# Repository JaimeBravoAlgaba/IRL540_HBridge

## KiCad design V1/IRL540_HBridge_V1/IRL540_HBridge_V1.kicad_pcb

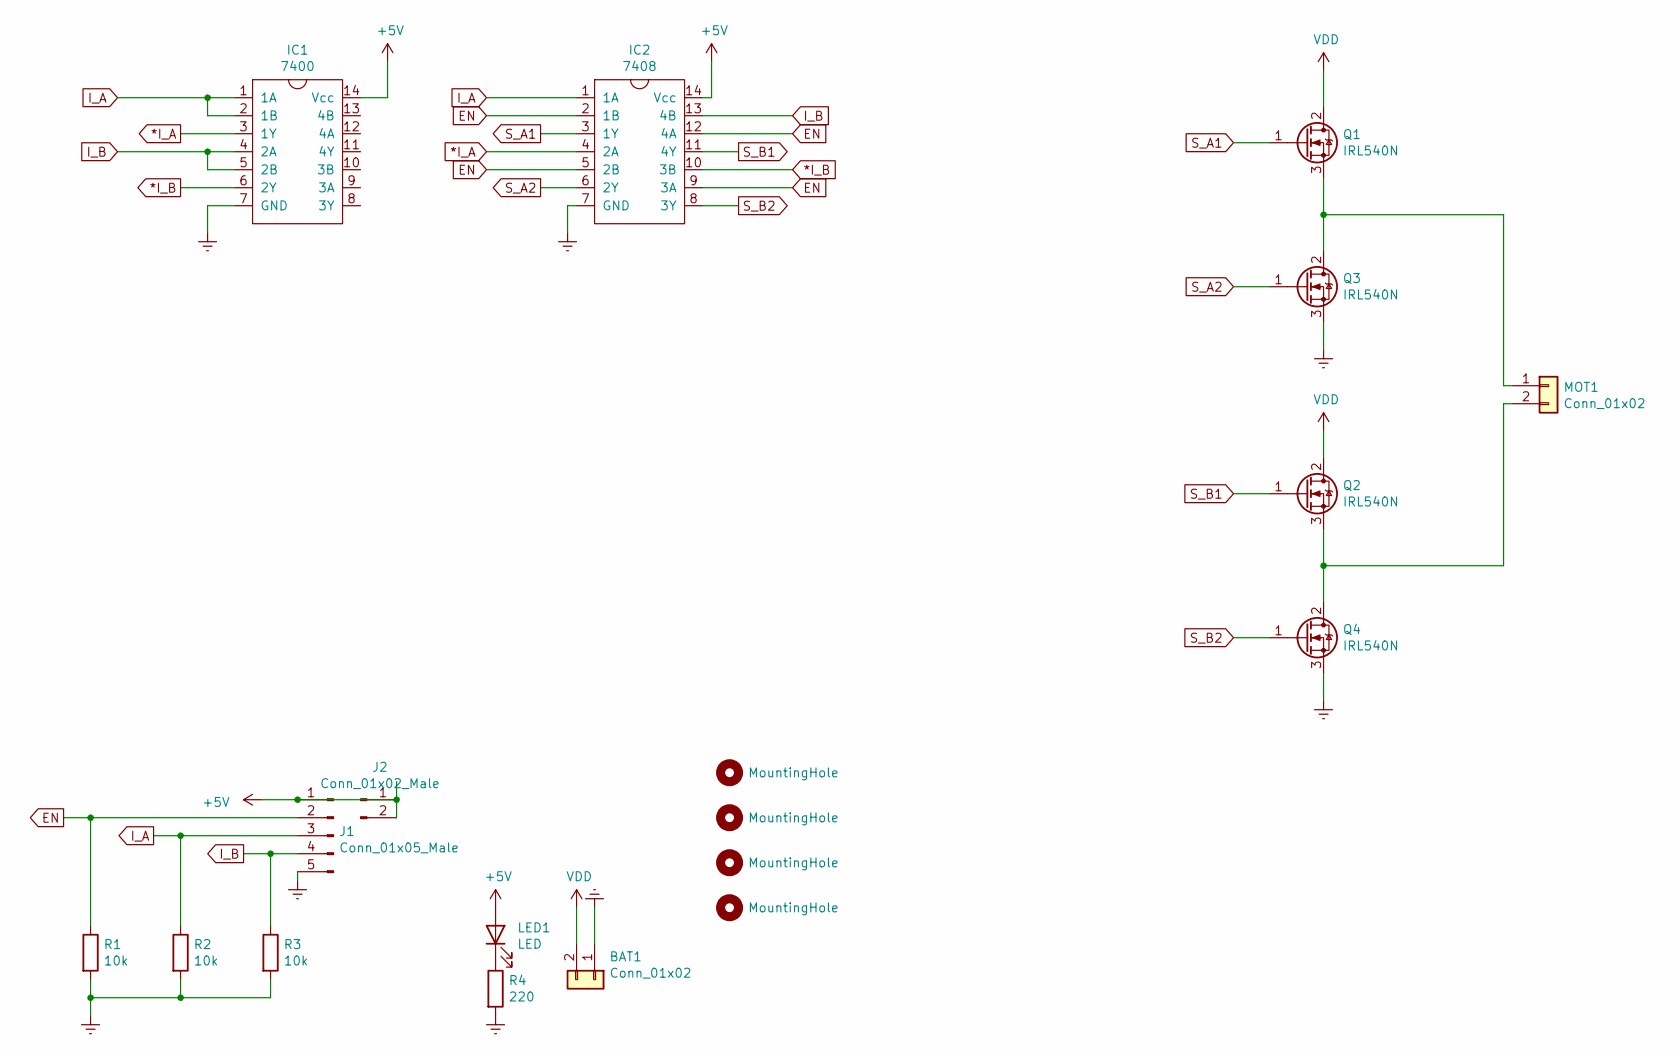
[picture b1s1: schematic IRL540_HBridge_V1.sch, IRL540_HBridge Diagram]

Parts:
BAT1: Conn_01x02; JWT_A3963_1x02_P3.96mm_Vertical
H1, H2, H3, H4: MountingHole; MountingHole_3.2mm_M3
IC1: 7400; DIP-14_W7.62mm
IC2: 7408; DIP-14_W7.62mm
J1: Conn_01x05_Male; PinHeader_1x05_P2.54mm_Vertical
J2: Conn_01x02_Male; PinHeader_1x02_P2.54mm_Vertical
LED1: LED; LED_D3.0mm
MOT1: Conn_01x02; JWT_A3963_1x02_P3.96mm_Vertical
Q1, Q2, Q3, Q4: IRL540N; TO-220-3_Vertical
R1, R2, R3: 10k; R_Axial_DIN0204_L3.6mm_D1.6mm_P5.08mm_Horizontal
R4: 220; R_Axial_DIN0204_L3.6mm_D1.6mm_P5.08mm_Horizontal

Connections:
*I_A: IC1.3 (1Y), IC2.4 (2A)
*I_B: IC1.6 (2Y), IC2.10 (3B)
+5V: IC1.14 (Vcc), IC2.14 (Vcc), J1.1, J2.1, J2.2, LED1.2 (A)
EN: IC2.2 (1B), IC2.5 (2B), IC2.9 (3A), IC2.12 (4A), J1.2, R1.1
GNDREF: BAT1.1, IC1.7 (GND), IC2.7 (GND), J1.5, Q3.3 (S), Q4.3 (S), R1.2, R2.2, R3.2, R4.2
I_A: IC1.1 (1A), IC1.2 (1B), IC2.1 (1A), J1.3, R2.1
I_B: IC1.4 (2A), IC1.5 (2B), IC2.13 (4B), J1.4, R3.1
unnamed: LED1.1 (K), R4.1
unnamed: MOT1.1, Q1.3 (S), Q3.2 (D)
unnamed: MOT1.2, Q2.3 (S), Q4.2 (D)
S_A1: IC2.3 (1Y), Q1.1 (G)
S_A2: IC2.6 (2Y), Q3.1 (G)
S_B1: IC2.11 (4Y), Q2.1 (G)
S_B2: IC2.8 (3Y), Q4.1 (G)
VDD: BAT1.2, Q1.2 (D), Q2.2 (D)

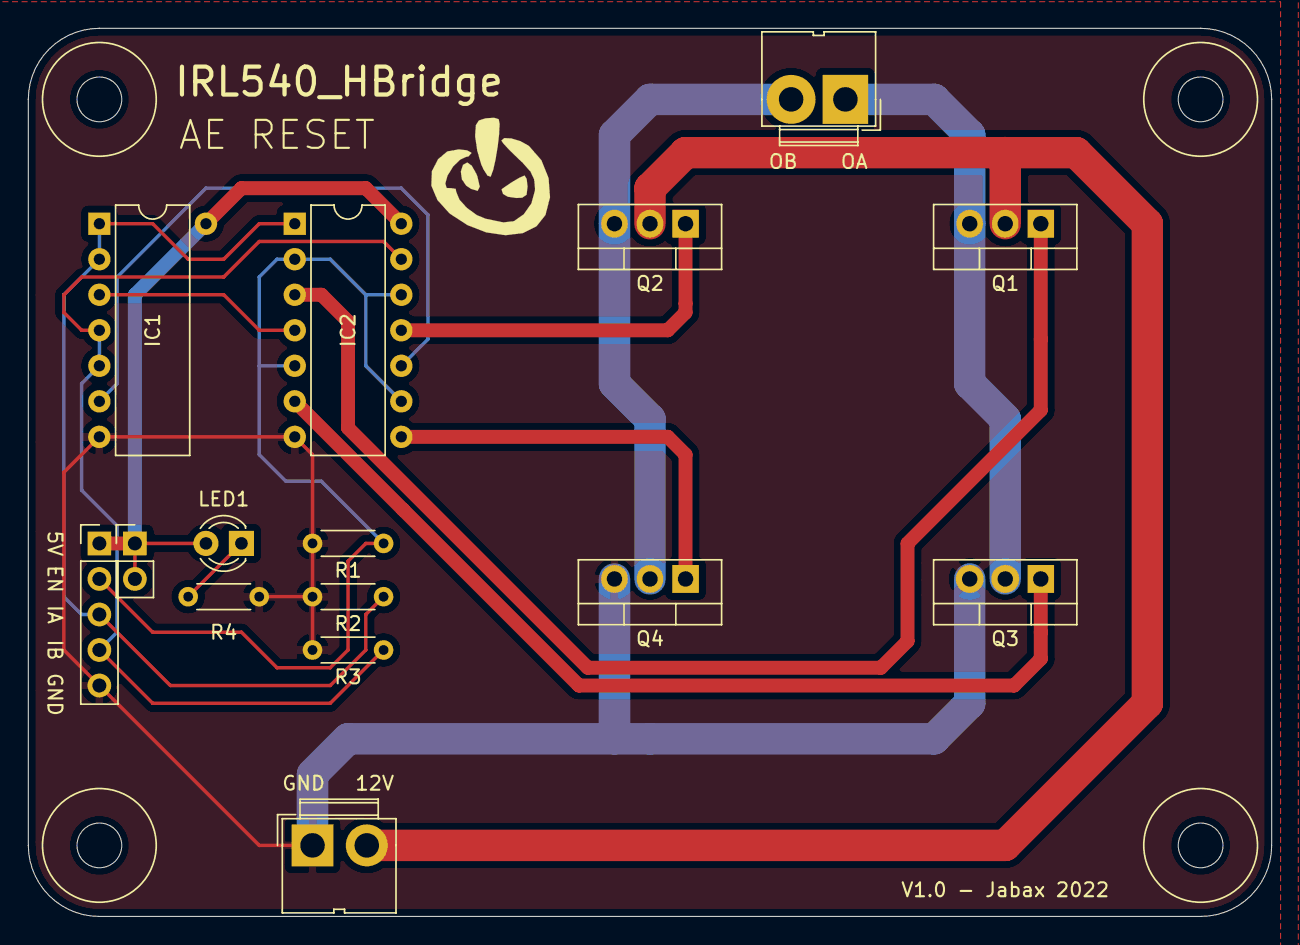
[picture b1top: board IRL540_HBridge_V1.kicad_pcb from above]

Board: 2 copper layers, 88.9 x 63.5 mm, 19 parts (0 on the bottom side), 15 nets.

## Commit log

2022-02-27 Diagrama del circuito.
2022-02-27 PCB sin enrutar.
2022-02-28 Enrutado y silks
2022-02-28 Versión 1.0!
